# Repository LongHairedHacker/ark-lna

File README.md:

ARK-LNA
=======
A low noise amplifier based on the MAR-6 or MAR-8.
It was designed with NOAA weather satellites in mind,
but might be useful for other VHF transmissions as well.

* Supply voltage: 6-10V
* Minimal center frequency: 87.16 MHz
* Maximal center frequency: 160 MHz
* Bandwidth: To be determined
* Gain: 20 dB

Parts
=====

| Count | Part				| Manufacturer Part	|
|-------|-------------------|-------------------|
|  2    | Trimmer 3-10pf	| TZC3R100A110R00 	|
|  2    | Inductor 330nH	| MLF2012DR33JTD25	|
|  1    | 33pF 0805         | CL21C330JBANNNC   |
|  1    | Inductor 10uH		| LBR2012T100K      |
|  1    | 91 Ohm 0603       | RC0603JR-0791RL   |
|  1    | 100pF 0805        | C0805C101J5GACTU  |
|  2    | 10uF              | UUT1V100MCL1GS    |
|  2    | 100nF 0603        | CL03A104KQ3NNNH   |
|  1    | Voltage regulator | LM1117-5          |
|  1    | amplifier         | MAR-6 / MAR-8     |
|  1    | case              | TEKO 371          |

Notes
=====
* Case inner dimensions: 46.5mm x 50.5mm
* MAR-6+
    * Datasheet: http://194.75.38.69/pdfs/MAR-6+.pdf
    * Layout suggestions: https://www.minicircuits.com/pcb/98-pl262.pdf

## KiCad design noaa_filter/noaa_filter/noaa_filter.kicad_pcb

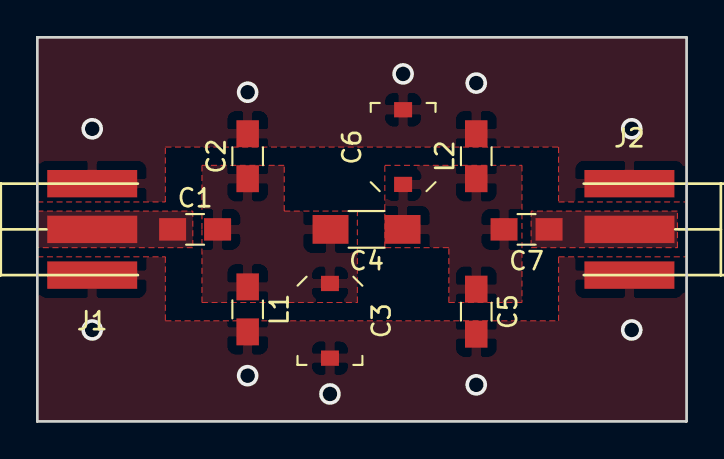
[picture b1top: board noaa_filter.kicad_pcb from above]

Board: 2 copper layers, 36.1 x 21.3 mm, 11 parts (0 on the bottom side), 5 nets, no tracks yet.

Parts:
C1, C7: 4.7pF; C_0805_HandSoldering
C2, C5: 10pF; C_0805_HandSoldering
C3, C6: 2-6pF; C_Trimmer_Murata_TZC3
C4: 1pF; C_1206_HandSoldering
J1, J2: Conn_Coaxial; SMA-boardedge
L1, L2: 64nH; C_0805_HandSoldering

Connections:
GND: C2.2, C3.2, C5.2, C6.2, J1.2, J2.2, L1.2, L2.2
unnamed: C1.1, J1.1
unnamed: C1.2, C2.1, C3.1, C4.2, L1.1
unnamed: C4.1, C5.1, C6.1, C7.2, L2.1
unnamed: C7.1, J2.1

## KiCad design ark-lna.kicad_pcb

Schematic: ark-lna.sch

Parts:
C1, C6: 10uF
C2: 100nf
C3: 3-10pfF
C4: 33pF
C5: 100nF
C7: 3-10pF
C8: 100pF
L1, L2: 401nF
L3: 10uH
P1, P2: CONN_1
R1: 91
U1: LM1117-5; TO-263
U2: MAR-6+; VV105

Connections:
+5V: C5.1, C6.1, R1.1, U1.2 (OUT)
GND: C1.2, C2.2, C4.2, C5.2, C6.2, U1.1 (ADJ), U2.2 (GND), U2.4 (GND); also elsewhere on the board
unnamed 2: C1.1, C2.1, U1.3 (IN); also elsewhere on the board
unnamed: C3.1, C4.1, L2.1
unnamed: C3.2, L1.2
unnamed: C7.1, U2.1 (RF_in)
unnamed: C7.2, L2.2
unnamed: C8.1, P2.1
unnamed: C8.2, L3.2, U2.3 (RF_out)
unnamed: L1.1, P1.1
unnamed: L3.1, R1.2

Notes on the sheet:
MAR-6 needs 16mA at 3.5v V_R_bias = 5v - 3.5v = 1.5v R_bias = 1.5v / 16mA = 93.75Ohm
LC series filter Impedance is minimal at f_0 = 1 / (2pi * sqrt(L * C)) Minimal f_0 using 10pf: 79.48 MHz Maximal f_0 using 3pf: 145.1 Mhz Use plastic screwdriver from scope probes to tune
C8 is chosen by fair dice roll. I'm open for suggestions for the proper way to choose it.

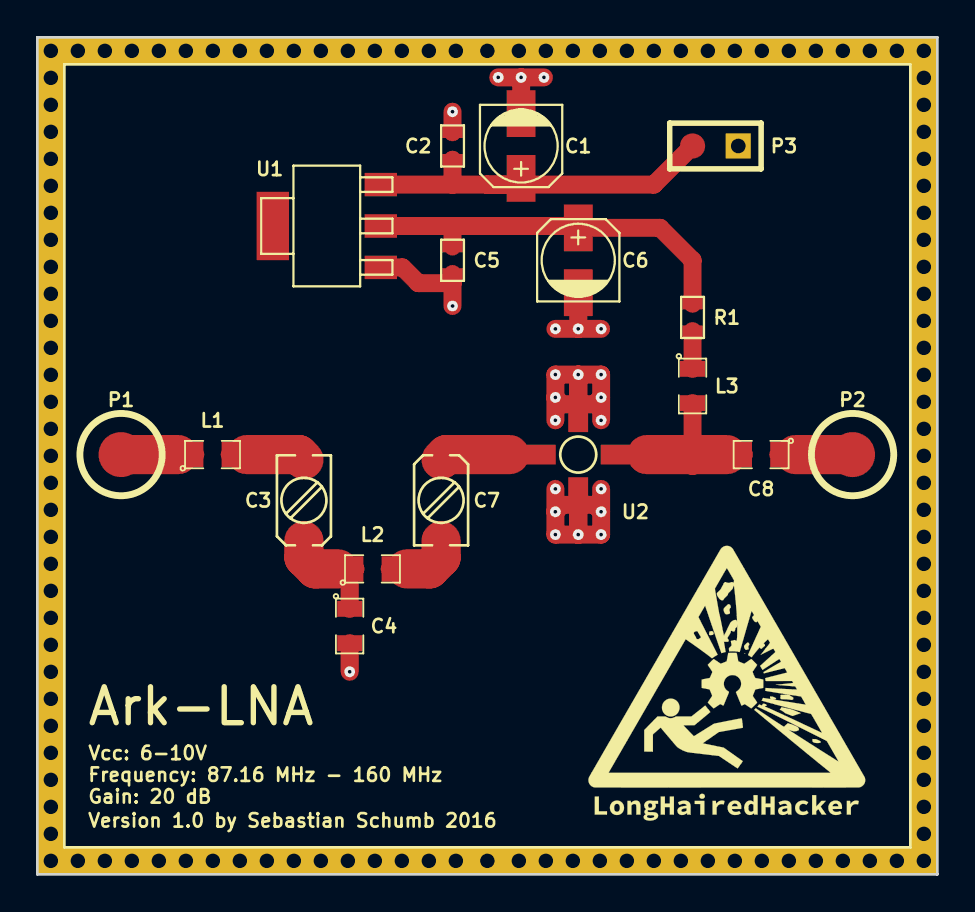
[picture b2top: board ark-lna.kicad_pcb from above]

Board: 2 copper layers, 50.0 x 46.5 mm, 18 parts (0 on the bottom side), 11 nets.

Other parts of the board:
P3: CONN_2; SIL-2
SHIELD1: CONN_1; teko371

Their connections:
GND: P3.1, SHIELD1.1; also elsewhere on the board
unnamed 2: P3.2; also elsewhere on the board

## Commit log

2016-06-06 Added schematic
2016-06-08 Started assigning footprints
2016-06-08 Exchanged inductors for better availability Started layouting
2016-06-09 Reduce size to a 50mm x 50mm PCB
2016-06-09 Minor cleanups
2016-06-09 finishing touches on silkscreen
2016-06-09 Added missing part numbers
2016-06-16 Fixed footprint for MAR-6
2016-07-07 Final tweaks and gerber export
2016-08-03 Added part count to README
2018-02-23 Added filter simulations
2018-03-03 Added filter pcb
2018-03-04 Working pcb
